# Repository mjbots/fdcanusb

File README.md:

# mjcanfd-usb-1x / fdcanusb

The mjcanfd-usb-1x and fdcanusb provide access to a CAN-FD bus using a
USB 2.0 full speed connection.  They present two possible interfaces:

1. A `gs_usb` interface compatible with the Linux kernel `gs_usb` socketcan driver
2. serial-like interface over the USB port using the CDC ACM class, i.e. a virtual COM port.

The designs and firmware are licensed under the Apache 2.0 License.

 * 

Pre-assembled hardware can be purchased at https://mjbots.com/products/fdcanusb

## Usage with moteus tools and libraries

To use a device with moteus tools or libraries, first install the
relevant udev rule following the instructions in the top of the file:

* [70-fdcanusb.rules](70-fdcanusb.rules)

Second, just use the application.  moteus utilities like
`moteus_tool`, `tview`, and the python and C++ libraries will
automatically discover any connected devices and use the CDC protocol.

## USB CDC Protocol

Each command or response is a single newline terminated line, composed
of 7-bit ASCII encoded characters.  Every command sent from the client
to the device has a response which consists of an optional command
specific response followed by a final line consisting solely of `OK` or
`ERR <details>`.

### States

The device can be in one of two states.

1. *Bus Off*: This is the initial state of the device.  In this state,
no frames may be sent or received, but the device may be configured.

2. *Bus On*: In this state frames may be sent and received, but
configuration is locked out.

## Commands

Sample commands are prefixed with `>` to show the data sent from the
client to the device and `<` to show the values sent from the device
to the client.  Those characters are for illustrative purposes only,
and are not present in actual communications.

### *conf*

The "conf" command is used to read and set configuration values.  It
has several subcommands.

#### *conf enumerate*

This emits all current configuration values one after another.

#### *conf get*

This queries the value of one specific configuration item.

```
>conf get sample.value
<31235
<OK
```

#### *conf set*

This sets the value of one specific configuration itme.

```
>conf set sample.value 1234
<OK
```

#### *conf load*

This loads all persistent configuration from the persistent storage.

```
>conf load
<OK
```

#### *conf write*

This stores all configuration values to persistent storage.  They will
then be the default when the device is powered on the in the future.

```
>conf write
<OK
```

#### *conf default*

Reset all configuration values to their "default" state.

```
>conf default
<OK
```

### can

#### *can on*

Enter the "Bus On" state.  All configurable values are validated and
put into place.  This results in an error if the device is already in
the "Bus On" state.

#### *can off*

Enter the "Bus Off" state.  Transmission and reception of CAN messages
is halted, and configurable values may be changed.

#### *can std*

Send a standard CAN frame.  The following format is used.

`can std <HEXID> <HEXDATA> <options>`

`options` may be zero or more of the following optionally separated by
spaces.

1. *B/b* require/disable bitrate switching
2. *F/f* require/disable FDCAN format
3. *R/r* require/disable remote frame

#### *can ext*

Send an extended CAN frame.  The following format is used.

`can ext <HEXID> <HEXDATA> <options>`

The allowable options are the same as for `can std`.

#### *can send*

Just like `std` or `ext`, but auto-detect the ID type.

#### *can status*

Report the current mode and status of various flags.

```
>can status
<mode:BUSON
<OK
```

### Receiving CAN Frames

When in the "Bus On" state, the device may spontaneously emit the
following lines upon receipt of valid CAN frames or other errors.

#### *rcv*

A CAN frame has been received.

```
<rcv <HEXID> <HEXDATA> <flags>
```

`flags` may be zero of more of the following separated by spaces:

1. *E/e* frame was received with extended/classic ID
1. *B/b* frame was received with/without bitrate switching
2. *F/f* frame was received in fdcan/classic mode
3. *R/r* frame was remote/data frame
4. tNNNNN timestamp of receipt measured in microseconds
5. fNN integer ID of which filter matched this frame

### Configurable Values

The following items may be configured.

* *can.bitrate* - The bitrate used for the CAN frame (or header only
  if bitrate switching is used.
* *can.fd_bitrate* - The bitrate used for the data and CRC field when
  bitrate switching is used.
* *can.sample_point* - The sample point for the nominal part of the
  CAN frame.  moteus requires 0.666, some other systems default to
  0.75, 0.8, or 0.87.
* *can.fd_sample_sample* - The sample point for the data (BRS) part of
  the CAN frame.  moteus requires 0.666, other systems may require
  alternate settings.
* *can.automatic_retransmission* - When true/non-zero, frames will be
  retried until acknowledged.
* *can.fdcan_frame* - By default, send frames in FDCAN mode
* *can.bitrate_switch* - By default, switch to the `can.fd_bitrate`
  for the data and CRC fields.
* *can.restricted_mode* - Only transmit acknowledgements.
* *can.bus_monitor* - Transmit nothing.
* *can.termination* - Enable the onboard terminator
* *can.autostart* - Enter BusOn immediately at power-on
* *can.autorecover* - Automatically recover from bus off events

* *can.global.std_action*
* *can.global.ext_action*
* *can.global.remote_std_action*
* *can.global.remote_ext_action*
  * 0/1 - accept
  * 2 - reject

* *can.filter.N.id1* - first ID
* *can.filter.N.id2* - second ID or bitmask
* *can.filter.N.mode*
  * 0 - range
  * 1 - exact match
  * 2 - bitmask
* *can.filter.N.type*
  * 0 - standard
  * 1 - extended
* *can.filter.N.action*
  * 0 - disable
  * 1 - accept
  * 2 - reject

## gs_usb interface

To use the device with a socketcan driver on Linux, the normal socketcan utilities can be used.  For instance, to bring up an interface compatible with moteus (not usually required because moteus tools and libraries will by default use the CDC interface), you would do:

```bash
ip link set can0 up type can \
  bitrate 1000000 dbitrate 5000000 \
  sjw 10 dsjw 5 \
  sample-point 0.666 dsample-point 0.666 \
  fd on
```

Then, all messages received can be displayed with:

```bash
candump can0
```

## Building firmware

To build the firmware on an Ubuntu 22.04 or newer system.

```
sudo apt install curl openocd
./tools/bazel build //...
```

To flash:

```
./flash.py
```

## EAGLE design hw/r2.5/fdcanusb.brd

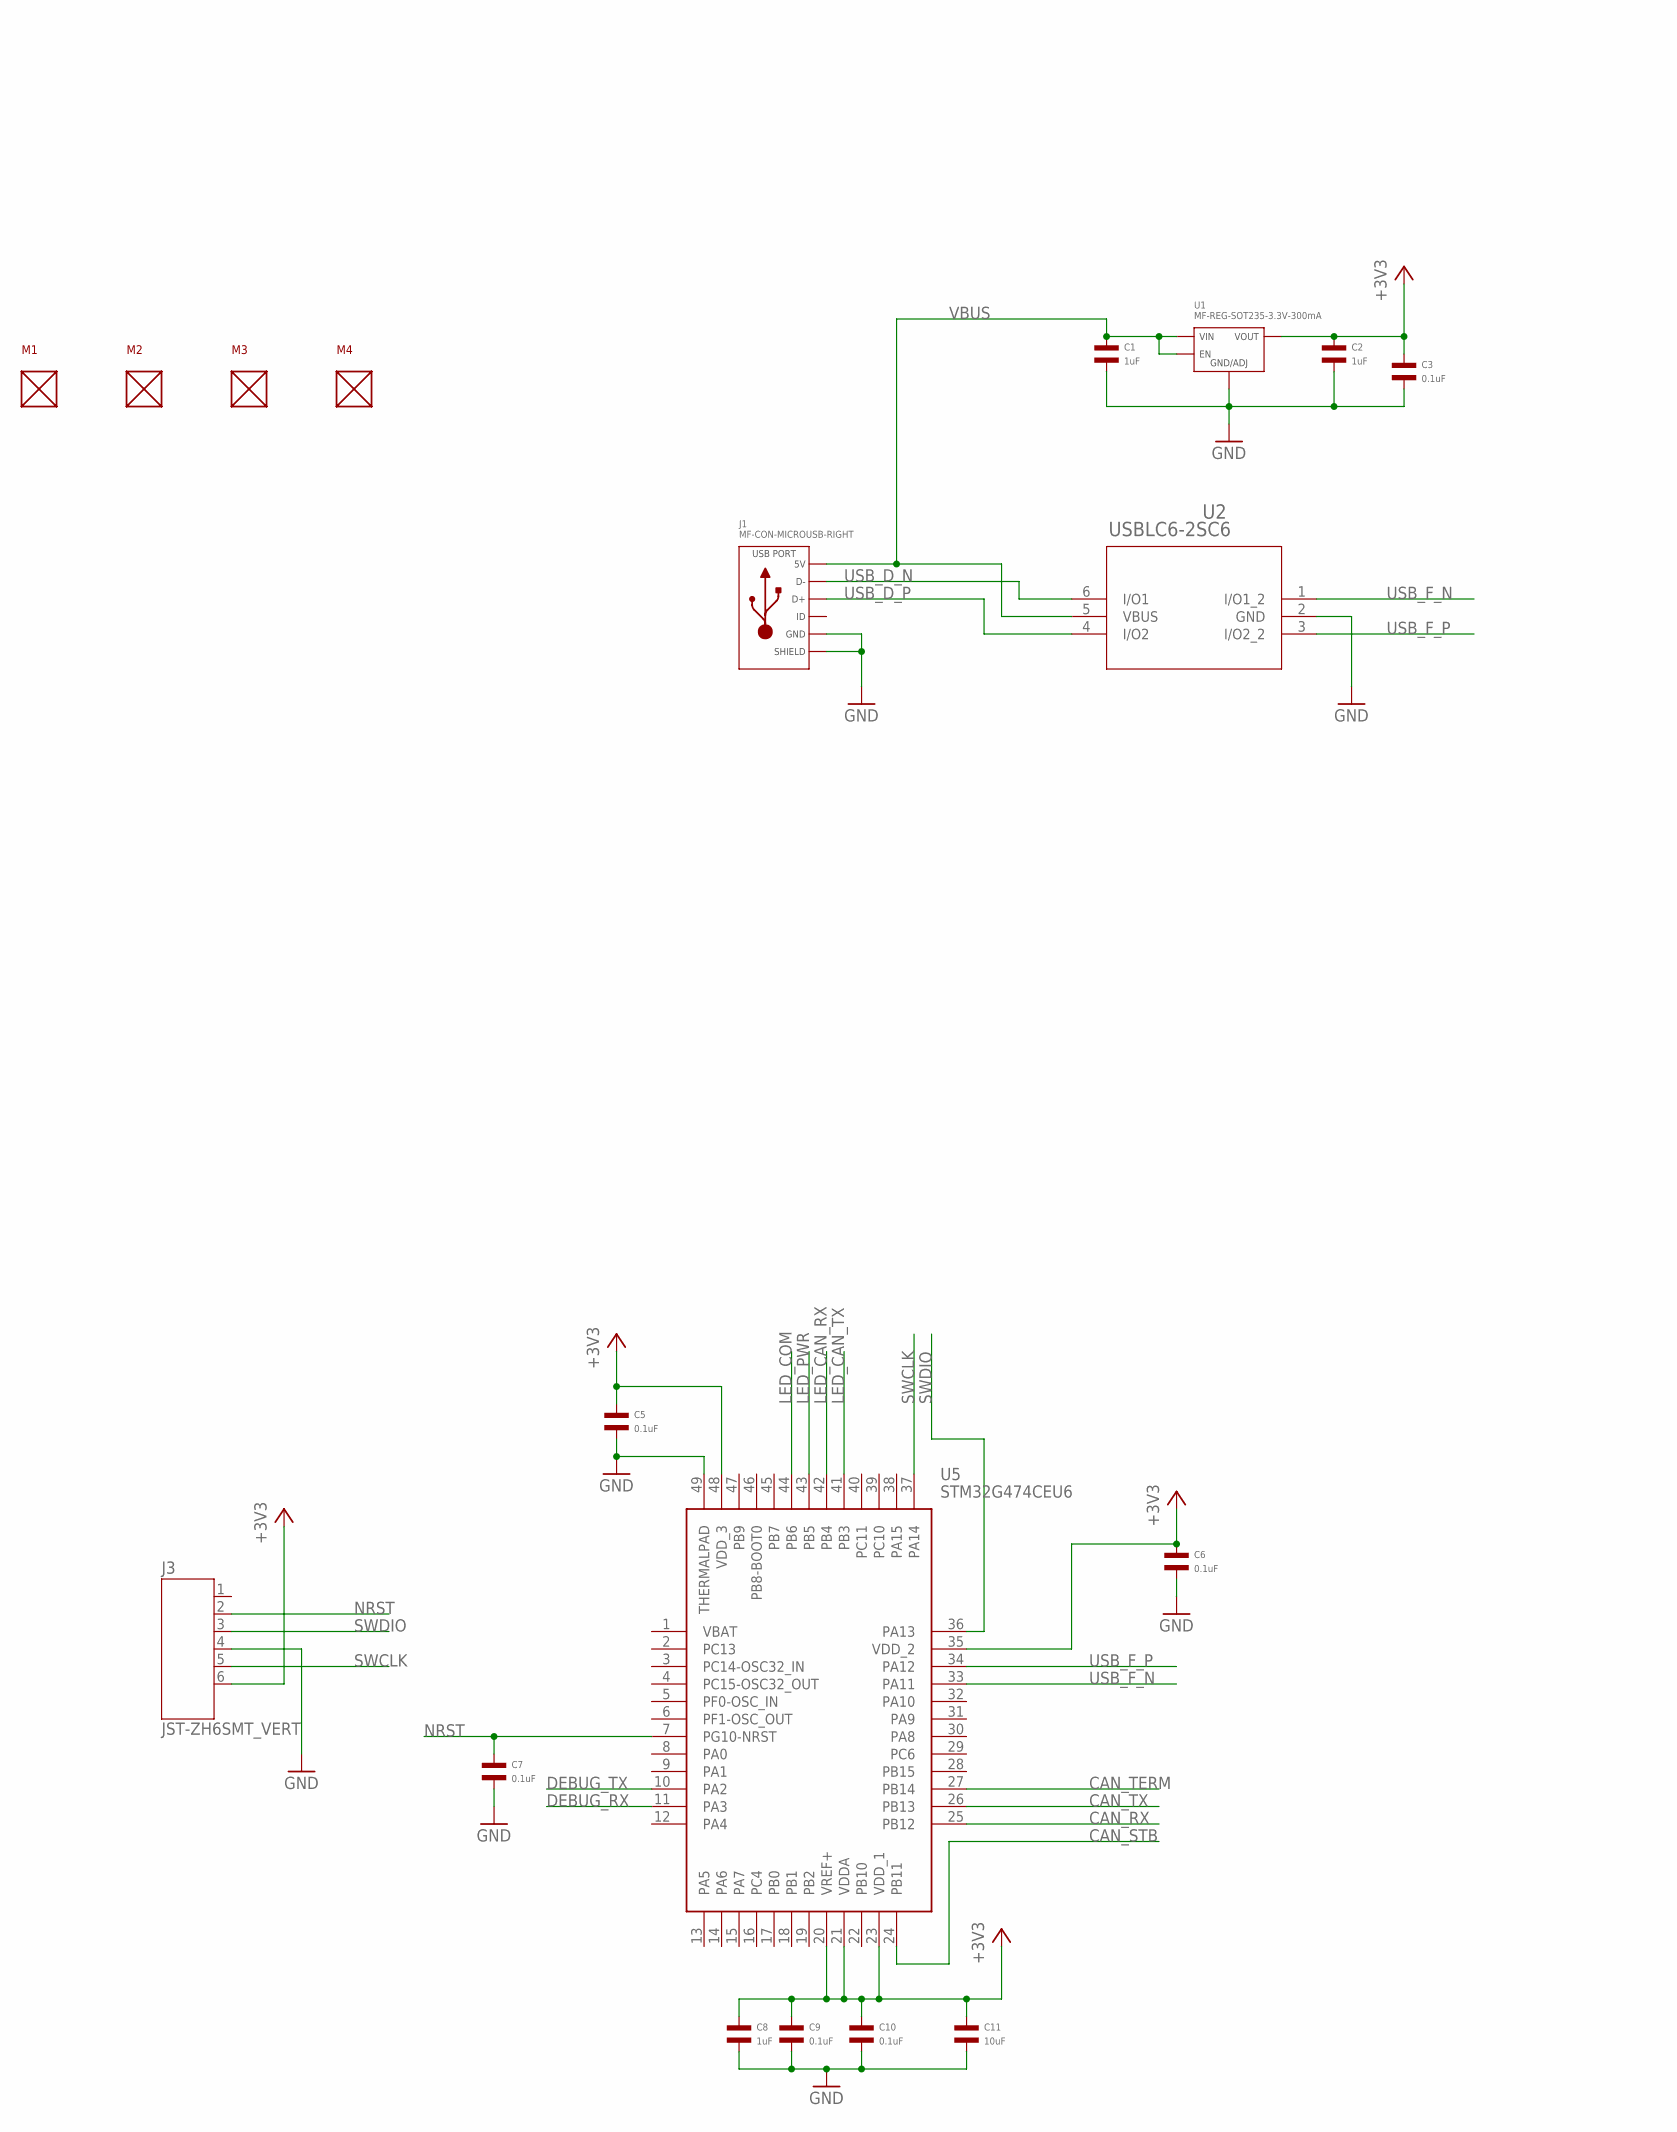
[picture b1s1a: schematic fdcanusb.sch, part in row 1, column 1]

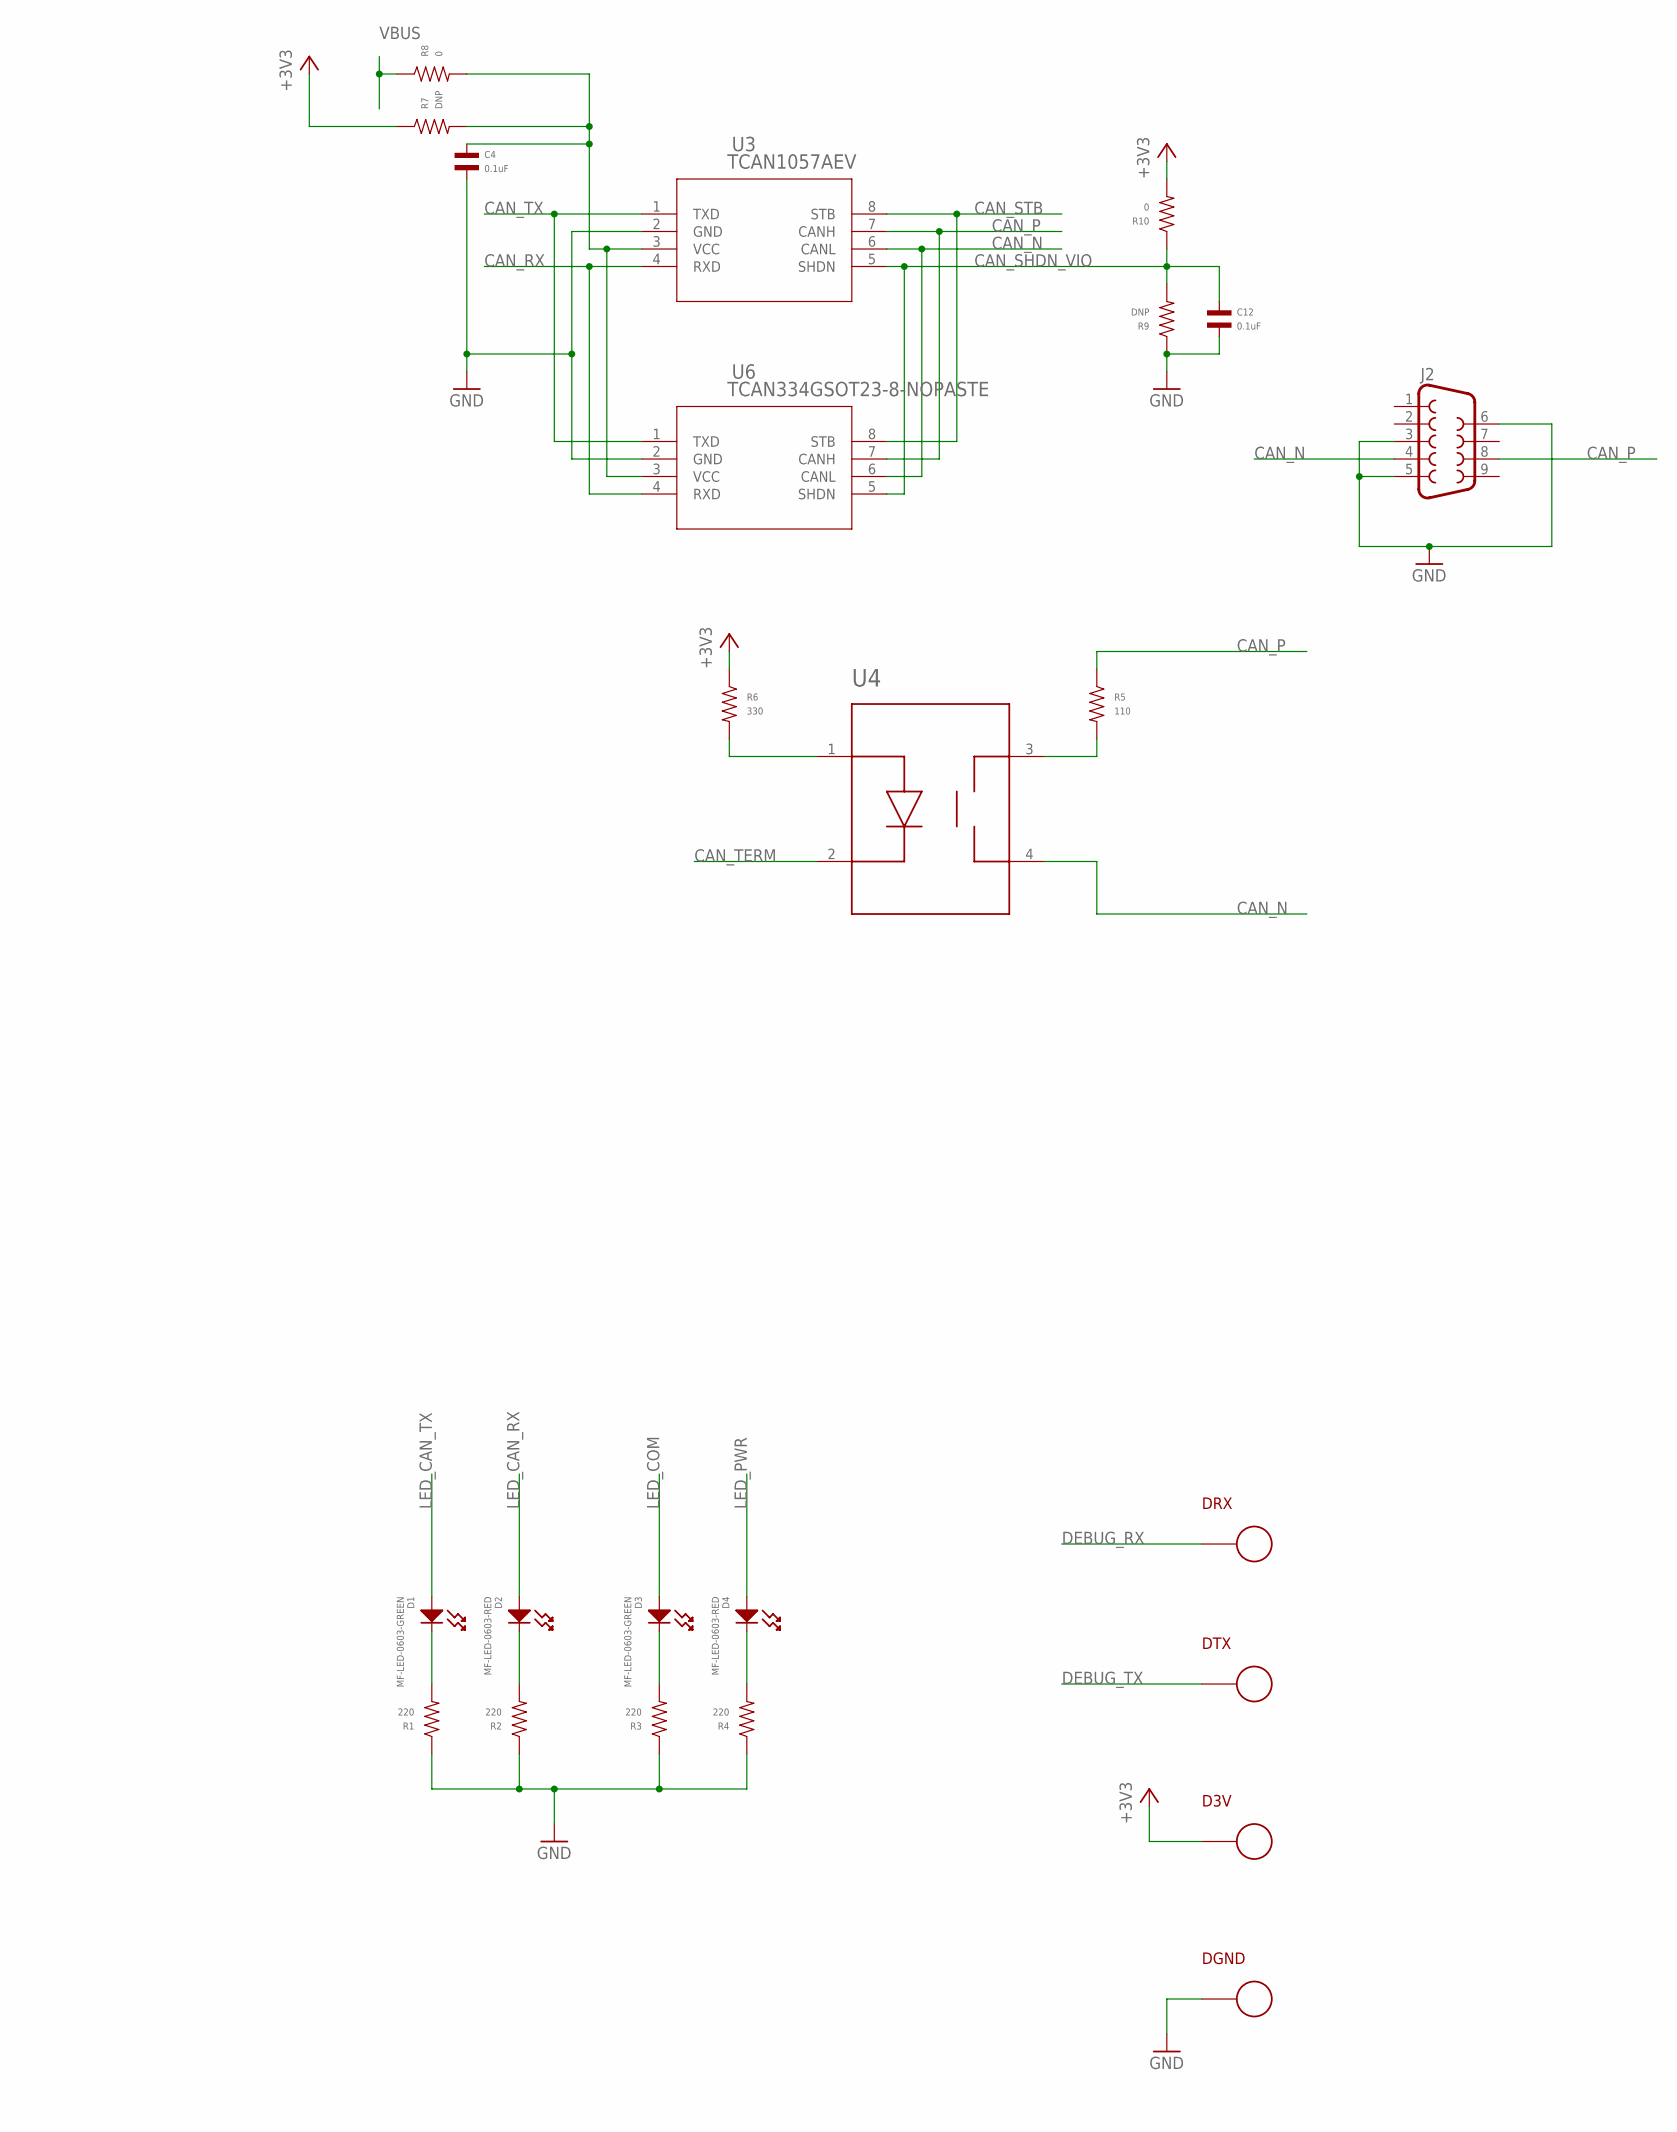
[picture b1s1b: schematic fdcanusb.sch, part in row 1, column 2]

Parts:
C1, C2, C8: 1uF; C0603; MPN MF-CAP-0603-1uF
C3, C4, C5, C6, C7, C9, C10, C12: 0.1uF; C0603; MPN MF-CAP-0603-0.1uF
C11: 10uF; C1206; MPN MF-CAP-1206-10uF
D1, D3: MF-LED-0603-GREEN; LED0603
D2, D4: MF-LED-0603-RED; LED0603
D3V: PAD24AWG_PAD; 24AWG_PAD
DGND: PAD24AWG_PAD; 24AWG_PAD
DRX: PAD24AWG_PAD; 24AWG_PAD
DTX: PAD24AWG_PAD; 24AWG_PAD
J1: MF-CON-MICROUSB-RIGHT; MICROUSB-RIGHT
J2: F09; DB09_PLATED
J3: JST-ZH6SMT_VERT; JST_B6B-ZR-SM4-TF(LF)(SN); MPN B6B-ZR-SM4-TF(LF)(SN)
M1, M2, M3, M4: MOUNT; M2.5MOUNT
R1, R2, R3, R4: 220; R0603; MPN MF-RES-0603-220
R5: 110; R0603; MPN RC0603FR-07110RL
R6: 330; R0603; MPN MF-RES-0603-330
R7, R9: DNP; R0603
R8, R10: 0; R0603; MPN MF-RES-0603-0
U1: MF-REG-SOT235-3.3V-300mA; SOT-23-5
U2: USBLC6-2SC6; SOT23-6L; MPN USBLC6-2SC6
U3: TCAN1057AEV; SOIC8; MPN TCAN1057AEVDRQ1
U4: TLP3317; MPN TLP3317
U5: STM32G474CEU6; QFN50P700X700X60-49N; MPN STM32G474CEU6
U6: TCAN334GSOT23-8-NOPASTE; SOT23-8-NOPASTE; MPN TCAN334GDCNT

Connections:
+3V3: C2.P$1, C3.P$1, C5.P$1, C6.P$1, C8.P$1, C9.P$1, C10.P$1, C11.P$1, D3V.P$1, J3.6, R6.P$1, R7.P$1, R10.P$2, U1.P$5 (VOUT), U5.20 (VREF+), U5.21 (VDDA), U5.23 (VDD_1), U5.35 (VDD_2), U5.48 (VDD_3)
CAN_N: J2.4, U3.6 (CANL), U4.4 (SW2), U6.6 (CANL)
CAN_P: J2.8, R5.P$1, U3.7 (CANH), U6.7 (CANH)
CAN_RX: U3.4 (RXD), U5.25 (PB12), U6.4 (RXD)
CAN_SHDN_VIO: C12.P$1, R9.P$2, R10.P$1, U3.5 (SHDN), U6.5 (SHDN)
CAN_STB: U3.8 (STB), U5.24 (PB11), U6.8 (STB)
CAN_TERM: U4.2 (CATHODE), U5.27 (PB14)
CAN_TX: U3.1 (TXD), U5.26 (PB13), U6.1 (TXD)
DEBUG_RX: DRX.P$1, U5.11 (PA3)
DEBUG_TX: DTX.P$1, U5.10 (PA2)
GND: C1.P$2, C2.P$2, C3.P$2, C4.P$2, C5.P$2, C6.P$2, C7.P$2, C8.P$2, C9.P$2, C10.P$2, C11.P$2, C12.P$2, DGND.P$1, J1.5 (GND), J1.S1 (SLD), J1.S2 (SLD), J1.S3 (SLD), J1.S4 (SLD), J1.S5 (SLD), J1.S6 (SLD), J2.3, J2.5, J2.6, J3.4, R1.P$1, R2.P$1, R3.P$1, R4.P$1, R9.P$1, U1.P$2 (GND/ADJ), U2.2 (GND), U3.2 (GND), U5.49 (THERMALPAD), U6.2 (GND)
LED_CAN_RX: D2.ANODE, U5.42 (PB4)
LED_CAN_TX: D1.ANODE, U5.41 (PB3)
LED_COM: D3.ANODE, U5.44 (PB6)
LED_PWR: D4.ANODE, U5.43 (PB5)
unnamed: C4.P$1, R7.P$2, R8.P$2, U3.3 (VCC), U6.3 (VCC)
unnamed: D1.CATHODE, R1.P$2
unnamed: D2.CATHODE, R2.P$2
unnamed: D3.CATHODE, R3.P$2
unnamed: D4.CATHODE, R4.P$2
unnamed: R5.P$2, U4.3 (SW1)
unnamed: R6.P$2, U4.1 (ANODE)
NRST: C7.P$1, J3.2, U5.7 (PG10-NRST)
SWCLK: J3.5, U5.37 (PA14)
SWDIO: J3.3, U5.36 (PA13)
USB_D_N: J1.2 (D-), U2.6 (I/O1)
USB_D_P: J1.3 (D+), U2.4 (I/O2)
USB_F_N: U2.1 (I/O1_2), U5.33 (PA11)
USB_F_P: U2.3 (I/O2_2), U5.34 (PA12)
VBUS: C1.P$1, J1.1 (5V), R8.P$1, U1.P$1 (VIN), U1.P$3 (EN), U2.5 (VBUS)

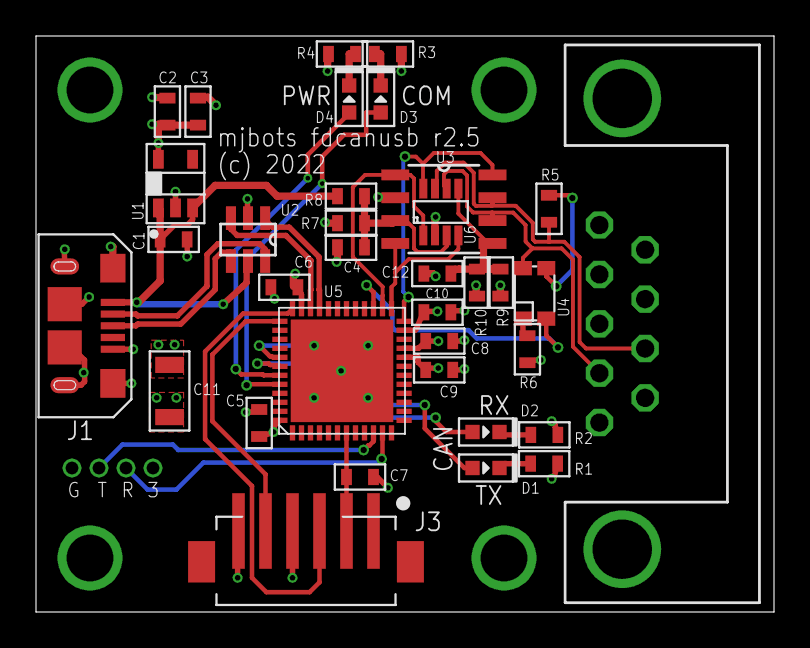
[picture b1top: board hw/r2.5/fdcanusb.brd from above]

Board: 4 copper layers, 41.0 x 32.0 mm, 43 parts (0 on the bottom side), 30 nets.

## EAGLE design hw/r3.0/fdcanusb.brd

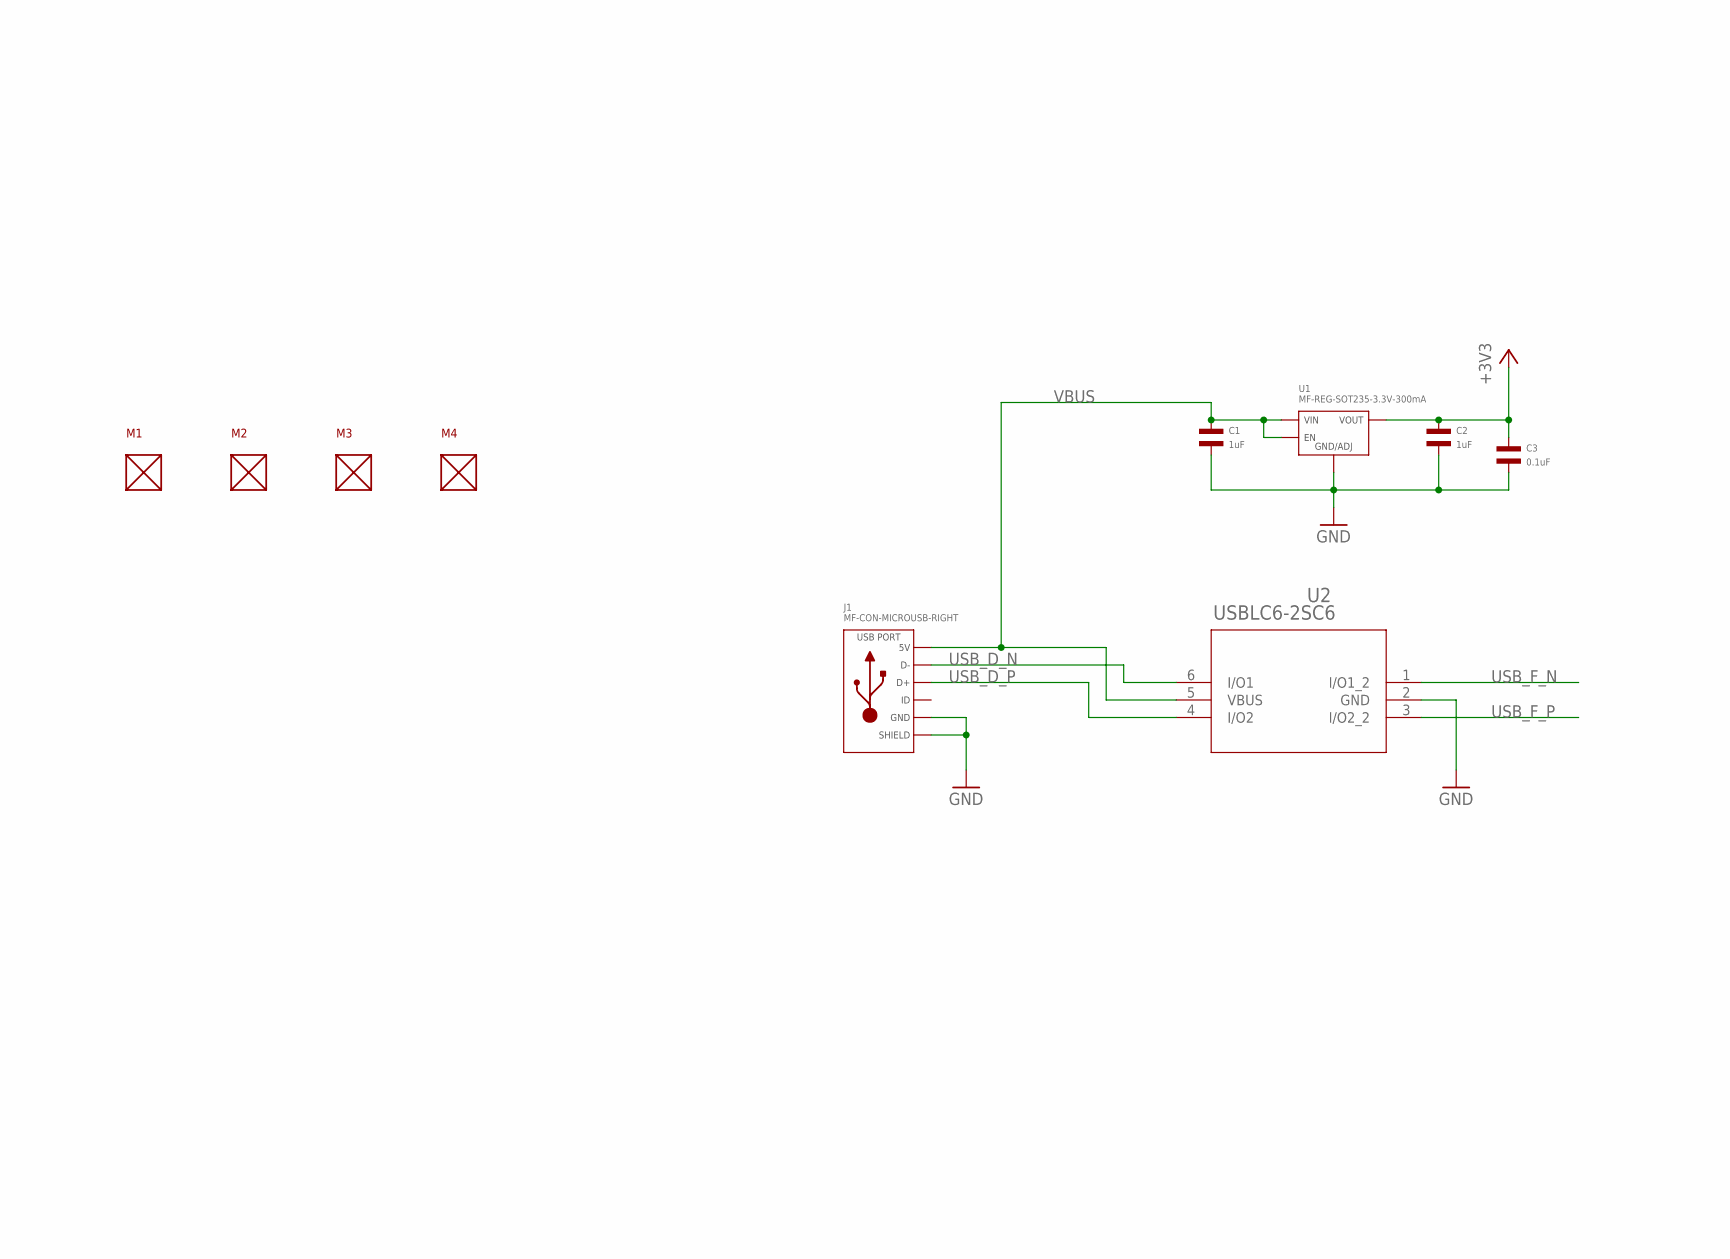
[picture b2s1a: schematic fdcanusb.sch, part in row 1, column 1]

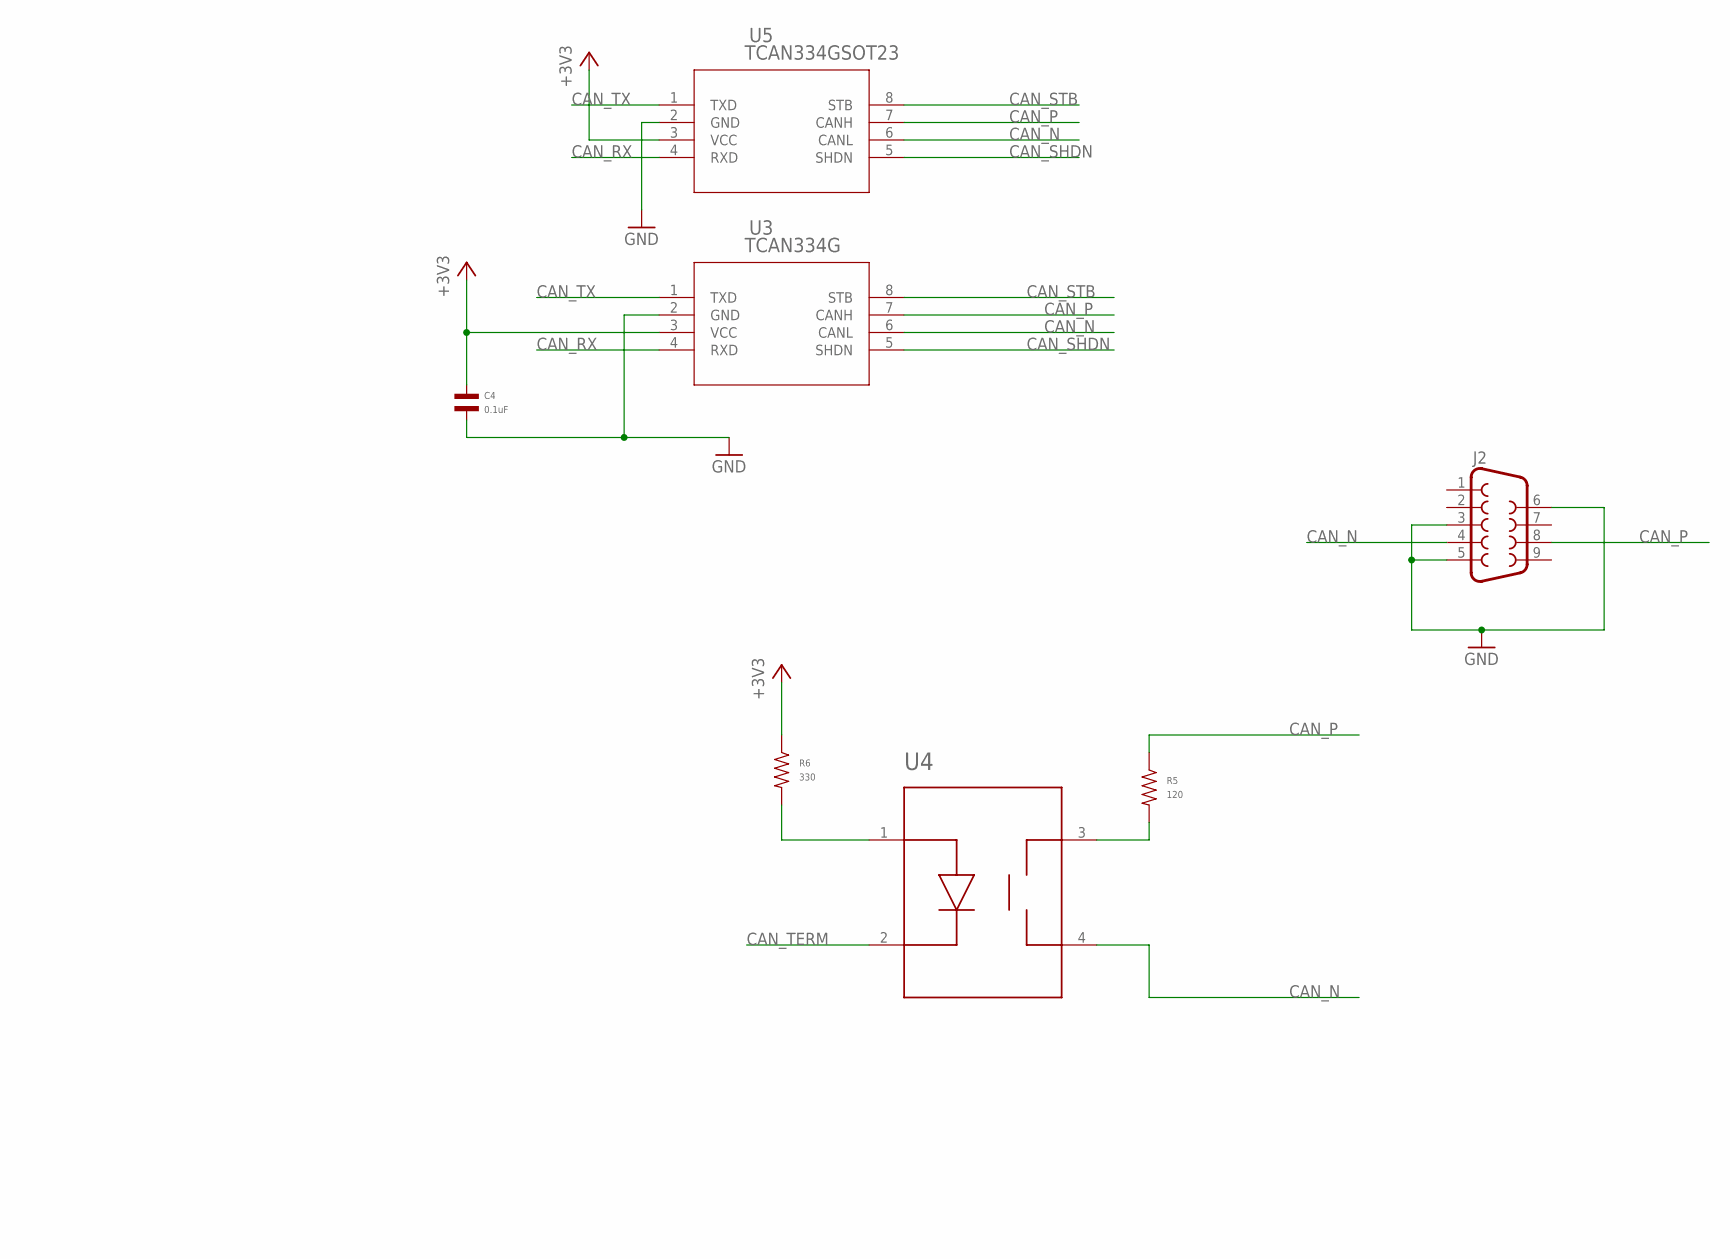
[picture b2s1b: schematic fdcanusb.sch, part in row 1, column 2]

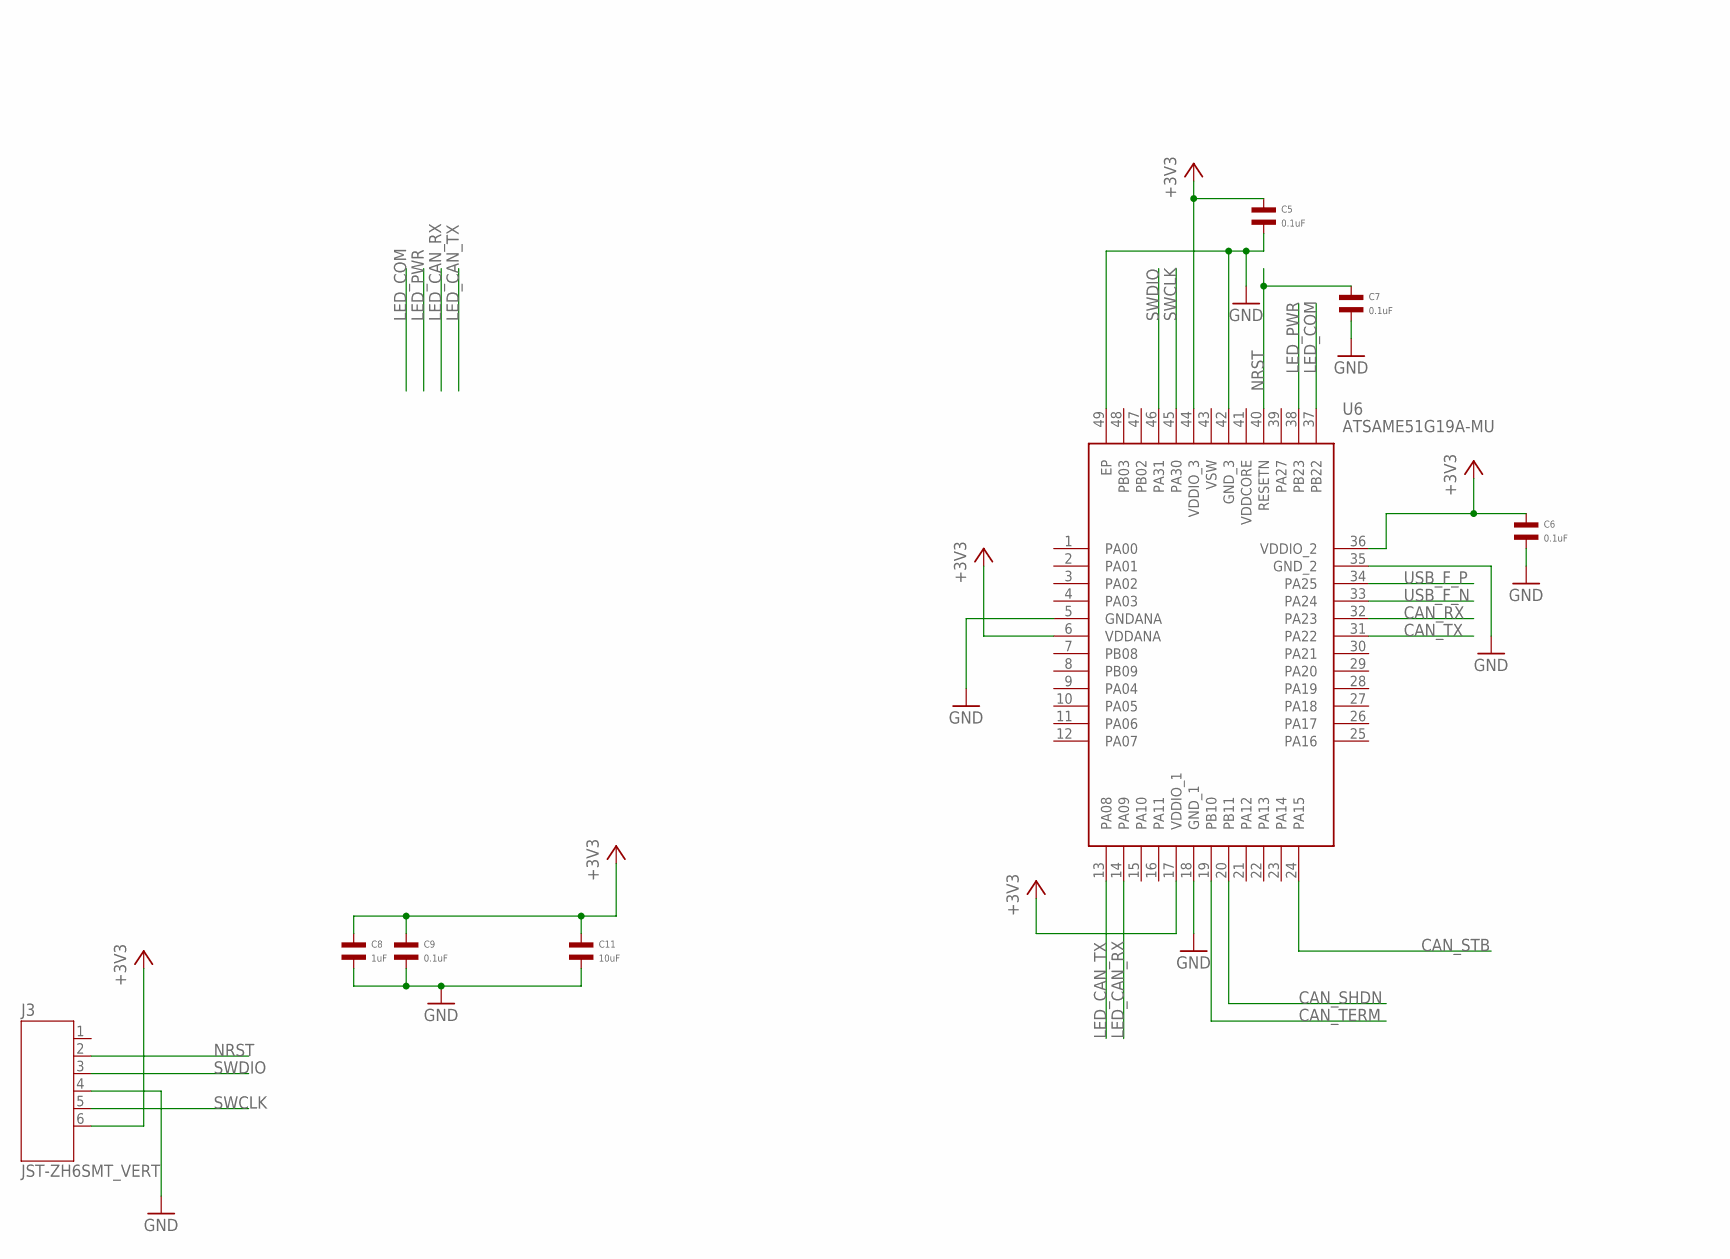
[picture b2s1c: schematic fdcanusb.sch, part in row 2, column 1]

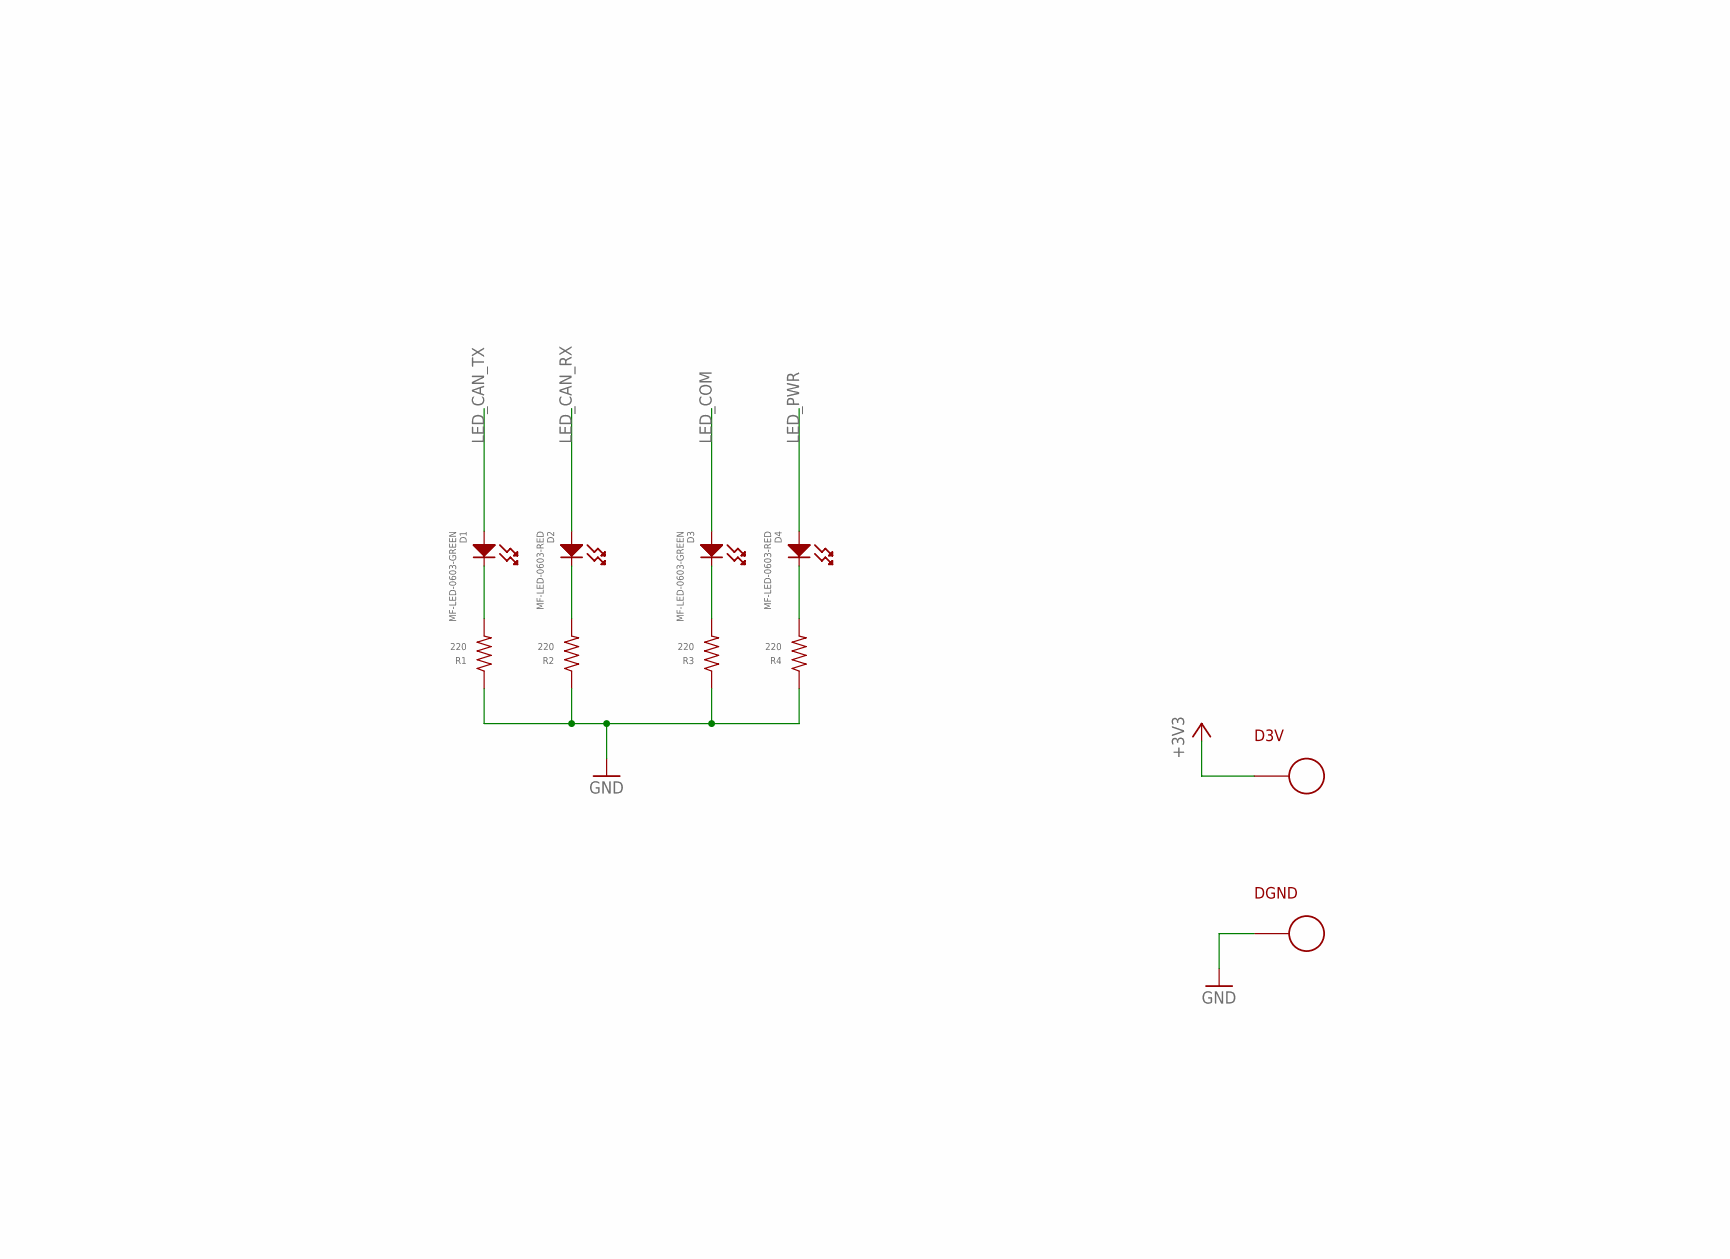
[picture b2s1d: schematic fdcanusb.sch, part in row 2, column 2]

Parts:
C1, C2, C8: 1uF; C0603; MPN MF-CAP-0603-1uF
C3, C4, C5, C6, C7, C9: 0.1uF; C0603; MPN MF-CAP-0603-0.1uF
C11: 10uF; C1206; MPN MF-CAP-1206-10uF
D1, D3: MF-LED-0603-GREEN; LED0603
D2, D4: MF-LED-0603-RED; LED0603
D3V: PAD24AWG_PAD; 24AWG_PAD
DGND: PAD24AWG_PAD; 24AWG_PAD
J1: MF-CON-MICROUSB-RIGHT; MICROUSB-RIGHT
J2: F09; DB09_PLATED
J3: JST-ZH6SMT_VERT; JST_B6B-ZR-SM4-TF(LF)(SN); MPN B6B-ZR-SM4-TF(LF)(SN)
M1, M2, M3, M4: MOUNT; M2.5MOUNT
R1, R2, R3, R4: 220; R0603; MPN MF-RES-0603-220
R5: 120; R0603; MPN RC0603FR-07120RL
R6: 330; R0603; MPN MF-RES-0603-330
U1: MF-REG-SOT235-3.3V-300mA; SOT-23-5
U2: USBLC6-2SC6; SOT23-6L; MPN USBLC6-2SC6
U3: TCAN334G; SOIC8; MPN TCAN330GDR
U4: TLP3317; MPN TLP3317
U5: TCAN334GSOT23; SOT23-8; MPN TCAN334GDCNT
U6: ATSAME51G19A-MU; QFN50P700X700X90-49N

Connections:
+3V3: C2.P$1, C3.P$1, C4.P$1, C5.P$1, C6.P$1, C8.P$1, C9.P$1, C11.P$1, D3V.P$1, J3.6, R6.P$1, U1.P$5 (VOUT), U3.3 (VCC), U5.3 (VCC), U6.6 (VDDANA), U6.17 (VDDIO_1), U6.36 (VDDIO_2), U6.44 (VDDIO_3)
CAN_N: J2.4, U3.6 (CANL), U4.4 (SW2), U5.6 (CANL)
CAN_P: J2.8, R5.P$1, U3.7 (CANH), U5.7 (CANH)
CAN_RX: U3.4 (RXD), U5.4 (RXD), U6.32 (PA23)
CAN_SHDN: U3.5 (SHDN), U5.5 (SHDN), U6.20 (PB11)
CAN_STB: U3.8 (STB), U5.8 (STB), U6.24 (PA15)
CAN_TERM: U4.2 (CATHODE), U6.19 (PB10)
CAN_TX: U3.1 (TXD), U5.1 (TXD), U6.31 (PA22)
GND: C1.P$2, C2.P$2, C3.P$2, C4.P$2, C5.P$2, C6.P$2, C7.P$2, C8.P$2, C9.P$2, C11.P$2, DGND.P$1, J1.5 (GND), J1.S1 (SLD), J1.S2 (SLD), J1.S3 (SLD), J1.S4 (SLD), J1.S5 (SLD), J1.S6 (SLD), J2.3, J2.5, J2.6, J3.4, R1.P$1, R2.P$1, R3.P$1, R4.P$1, U1.P$2 (GND/ADJ), U2.2 (GND), U3.2 (GND), U5.2 (GND), U6.5 (GNDANA), U6.18 (GND_1), U6.35 (GND_2), U6.42 (GND_3), U6.49 (EP)
LED_CAN_RX: D2.ANODE, U6.14 (PA09)
LED_CAN_TX: D1.ANODE, U6.13 (PA08)
LED_COM: D3.ANODE, U6.37 (PB22)
LED_PWR: D4.ANODE, U6.38 (PB23)
unnamed: D1.CATHODE, R1.P$2
unnamed: D2.CATHODE, R2.P$2
unnamed: D3.CATHODE, R3.P$2
unnamed: D4.CATHODE, R4.P$2
unnamed: R5.P$2, U4.3 (SW1)
unnamed: R6.P$2, U4.1 (ANODE)
NRST: C7.P$1, J3.2, U6.40 (RESETN)
SWCLK: J3.5, U6.45 (PA30)
SWDIO: J3.3, U6.46 (PA31)
USB_D_N: J1.2 (D-), U2.6 (I/O1)
USB_D_P: J1.3 (D+), U2.4 (I/O2)
USB_F_N: U2.1 (I/O1_2), U6.33 (PA24)
USB_F_P: U2.3 (I/O2_2), U6.34 (PA25)
VBUS: C1.P$1, J1.1 (5V), U1.P$1 (VIN), U1.P$3 (EN), U2.5 (VBUS)

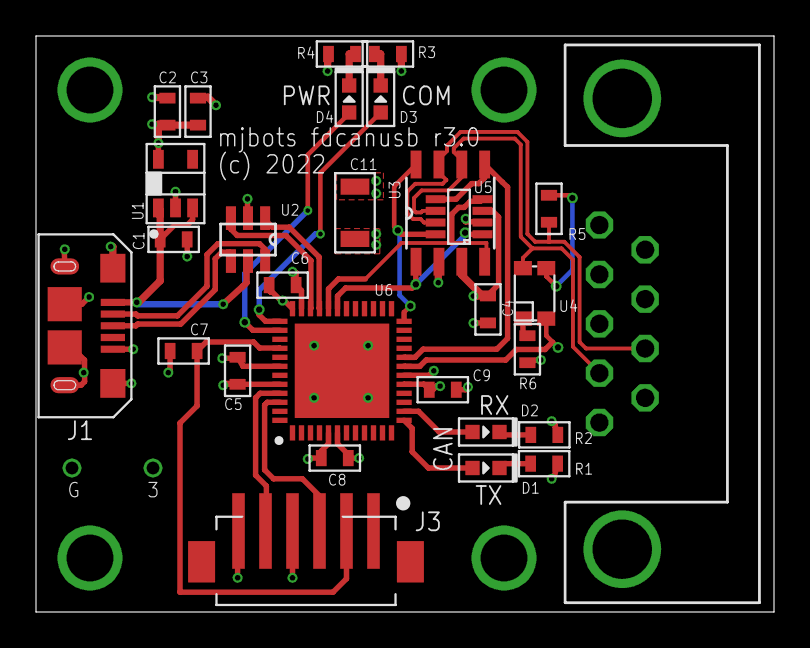
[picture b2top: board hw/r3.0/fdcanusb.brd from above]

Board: 4 copper layers, 41.0 x 32.0 mm, 35 parts (0 on the bottom side), 27 nets.

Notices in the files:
hw/fdcanusb.sch:
(c) 2022 Josh Pieper, jpieper@mjbots.com
https://www.apache.org/licenses/LICENSE-2.0
hw/r2.1/fdcanusb.sch:
(c) 2019 Josh Pieper, jjp@pobox.com
hw/r2.3/fdcanusb.sch:
(c) 2021 Josh Pieper, jpieper@mjbots.com
hw/r2.5/fdcanusb.brd:
(c) 2022
